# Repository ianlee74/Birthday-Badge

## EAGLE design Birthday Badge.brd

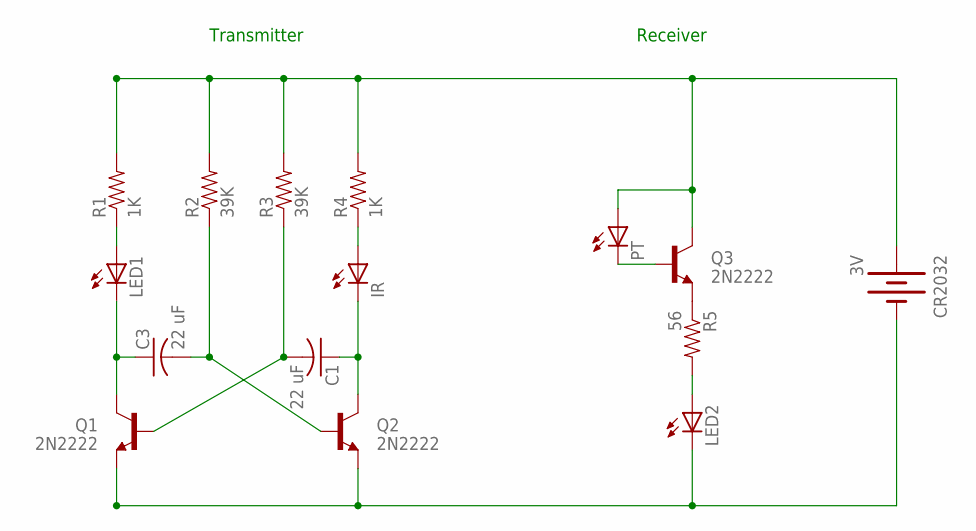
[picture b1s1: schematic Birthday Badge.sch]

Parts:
C1, C3: 22 uF; C1210K
CR2032: 3V; BATTCON_20MM
IR: LED5MM
LED1, LED2: LED5MM
PT: LED5MM
Q1, Q2, Q3: 2N2222; TO-92-AMMO
R1, R4: 1K; AXIAL-0.4
R2, R3: 39K; AXIAL-0.4
R5: 56; AXIAL-0.4

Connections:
unnamed: Q3.1 (E), R5.P$1 (1)
unnamed: CR2032.1 (+), PT.A, Q3.3 (C), R1.P$2 (2), R2.P$2 (2), R3.P$2 (2), R4.P$2 (2)
unnamed: PT.K (C), Q3.2 (B)
unnamed: CR2032.2 (-), LED2.K (C), Q1.1 (E), Q2.1 (E)
unnamed: LED1.A, R1.P$1 (1)
unnamed: C3.1, LED1.K (C), Q1.3 (C)
unnamed: IR.A, R4.P$1 (1)
unnamed: C1.1, IR.K (C), Q2.3 (C)
unnamed: C3.2, Q2.2 (B), R2.P$1 (1)
unnamed: C1.2, Q1.2 (B), R3.P$1 (1)
unnamed: LED2.A, R5.P$2 (2)

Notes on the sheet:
Transmitter
Receiver

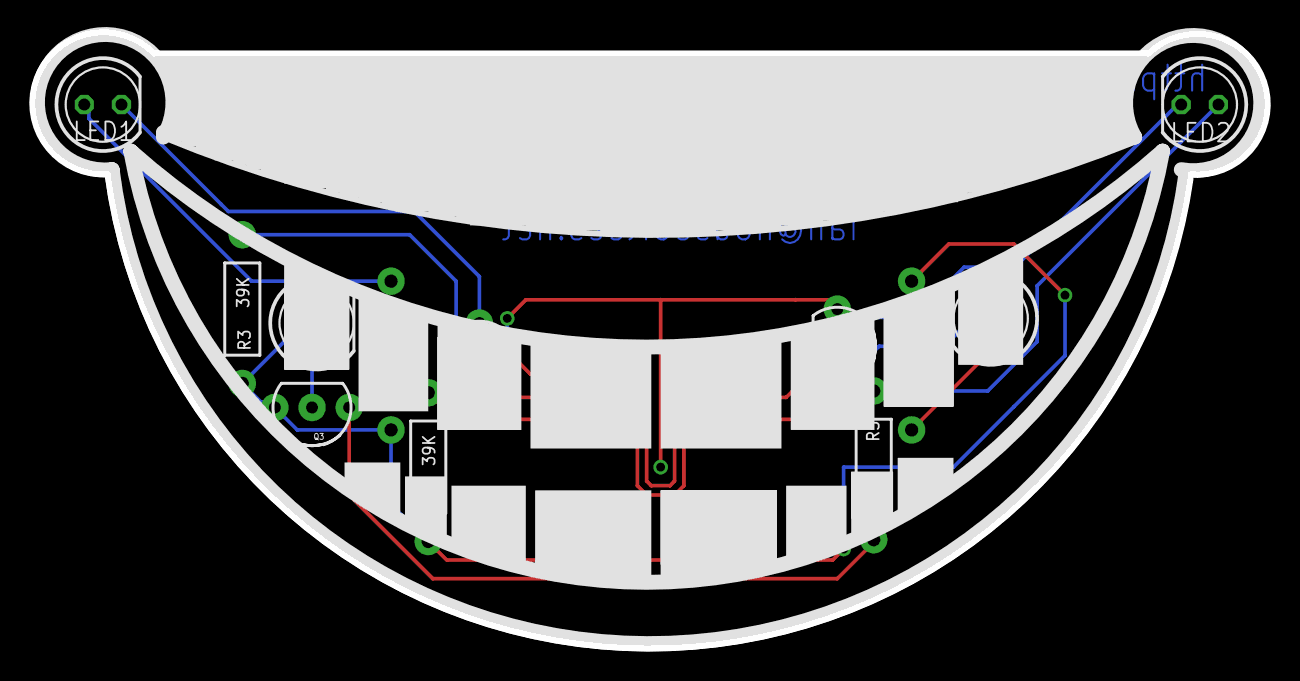
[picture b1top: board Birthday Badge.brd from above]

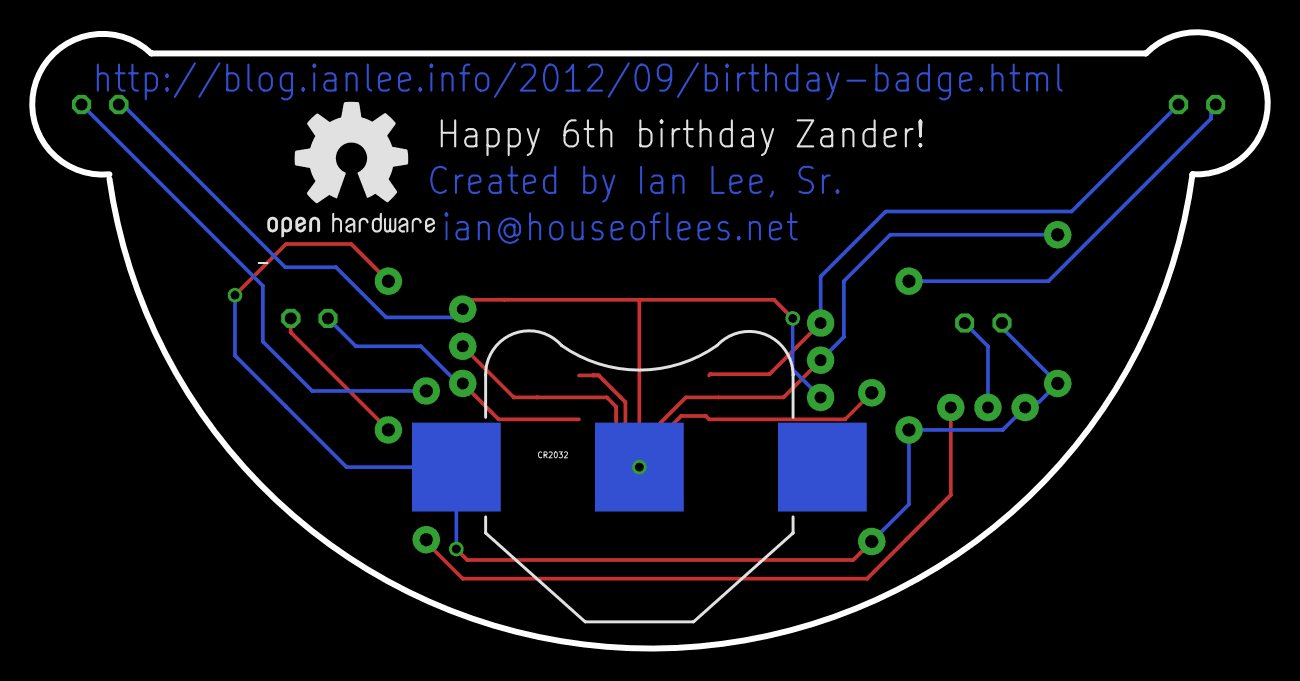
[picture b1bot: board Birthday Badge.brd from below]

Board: 2 copper layers, 84.4 x 42.1 mm, 16 parts (2 on the bottom side), 11 nets.

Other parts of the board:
U$1: OSHW1

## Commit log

2012-09-30 Initial commit.
2012-09-30 Added back side text.
2012-10-01 Fixed transistor that was overlapping battery holder.
2012-10-01 Adjusted text locations after viewing created Gerber files.
2012-10-02 Update .gitignore to ignore the CAM files.
2012-10-02 Added contact info to schematic.

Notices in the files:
parts and their libraries:
SparkFun: Licensing: CC v3.0 Share-Alike You are welcome to use this library for commercial purposes.
